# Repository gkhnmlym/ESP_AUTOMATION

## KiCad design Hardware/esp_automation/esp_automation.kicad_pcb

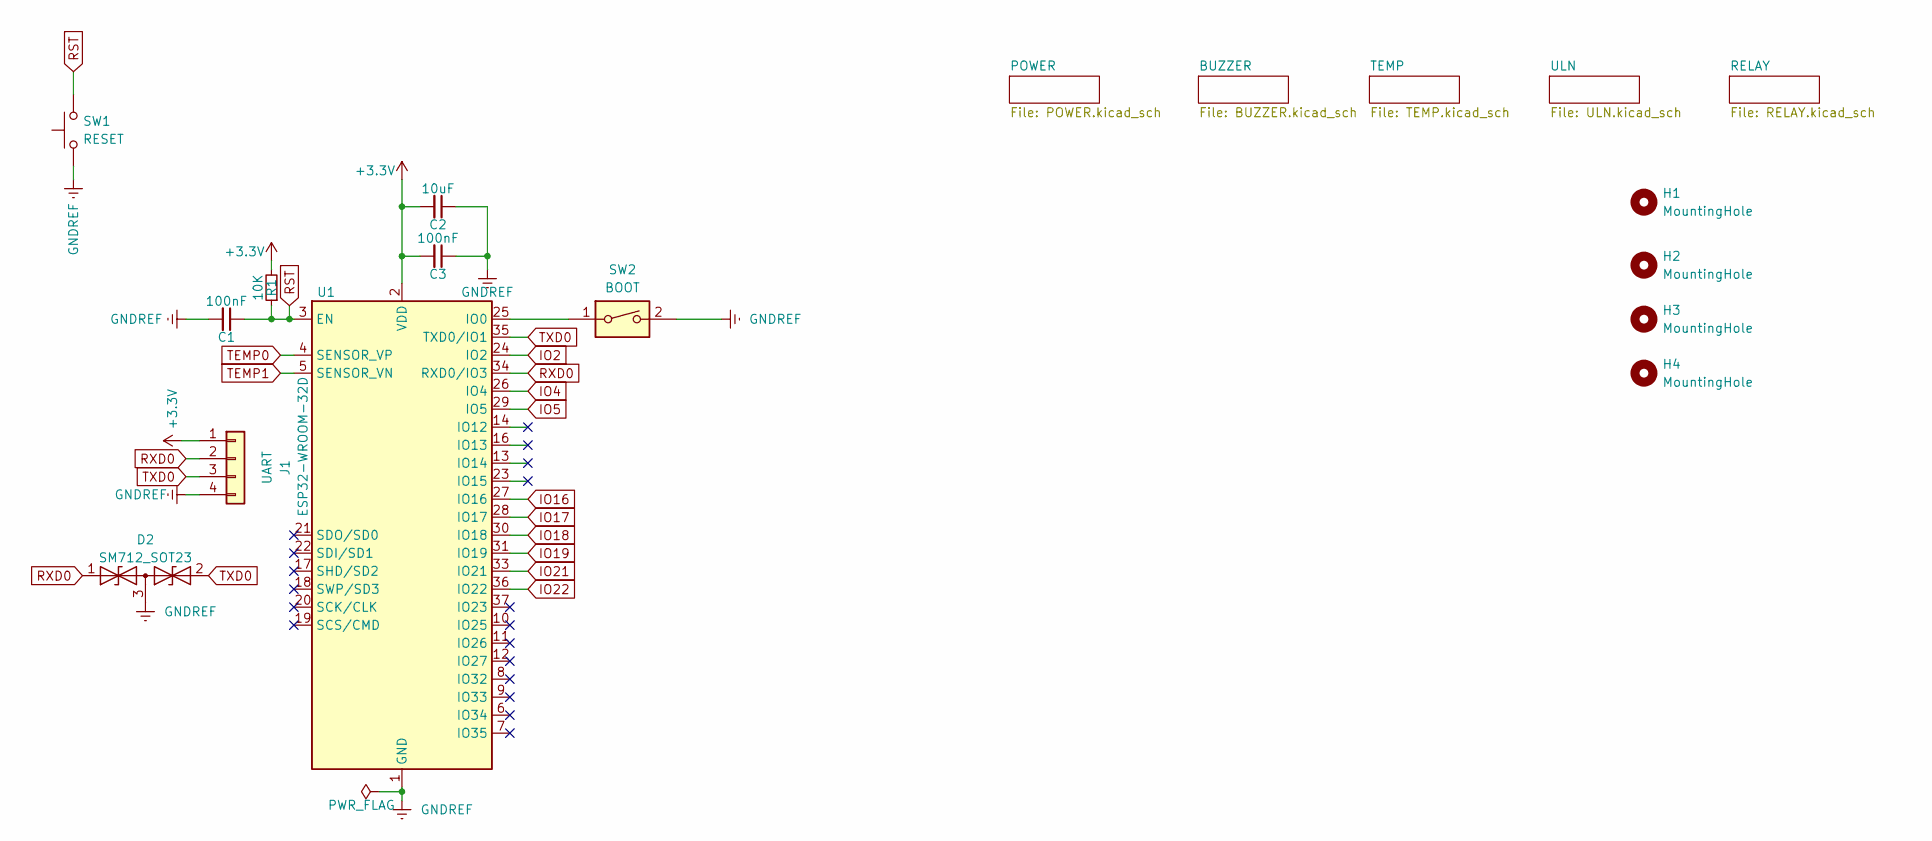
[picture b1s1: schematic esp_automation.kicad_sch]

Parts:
C1, C3: 100nF; C_0805_2012Metric
C2: 10uF; C_0805_2012Metric
D2: SM712_SOT23; SOT-23
H1, H2, H3, H4: MountingHole; MountingHole_3.2mm_M3_Pad_Via
J1: UART; PinHeader_1x04_P2.54mm_Vertical
R1: 10K; R_0805_2012Metric
SW1: RESET; SW_SPST_CK_RS282G05A3
SW2: BOOT; SW_DIP_SPSTx01_Slide_6.7x4.1mm_W6.73mm_P2.54mm_LowProfile_J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
U1: ESP32-WROOM-32D; ESP32-WROOM-32

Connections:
+3V3: C2.2, C3.2, J1.1, R1.2, U1.2 (VDD); also elsewhere on the board
IO2: U1.24 (IO2)
IO4: U1.26 (IO4); also elsewhere on the board
IO5: U1.29 (IO5); also elsewhere on the board
IO16: U1.27 (IO16); also elsewhere on the board
IO17: U1.28 (IO17); also elsewhere on the board
IO18: U1.30 (IO18); also elsewhere on the board
IO19: U1.31 (IO19); also elsewhere on the board
IO21: U1.33 (IO21); also elsewhere on the board
IO22: U1.36 (IO22); also elsewhere on the board
unnamed: SW2.1, U1.25 (IO0)
RST: C1.1, R1.1, SW1.2, U1.3 (EN)
RXD0: D2.1 (A1), J1.2, U1.34 (RXD0/IO3)
TEMP0: U1.4 (SENSOR_VP); also elsewhere on the board
TEMP1: U1.5 (SENSOR_VN); also elsewhere on the board
TXD0: D2.2 (A2), J1.3, U1.35 (TXD0/IO1)

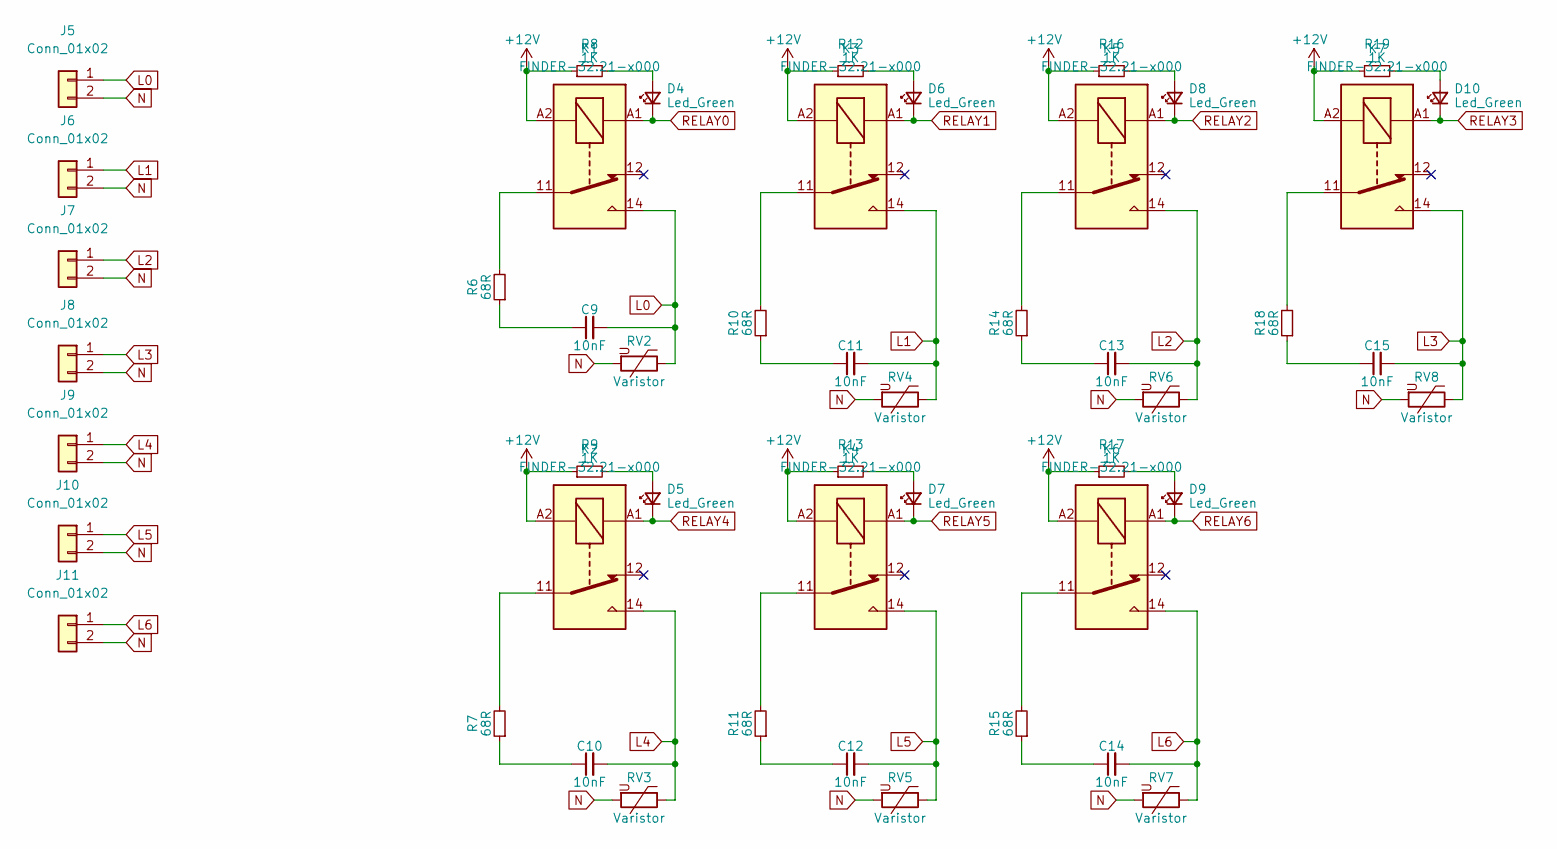
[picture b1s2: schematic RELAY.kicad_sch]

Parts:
C9, C10, C11, C12, C13, C14, C15: 10nF; C_Rect_L13.0mm_W4.0mm_P10.00mm_FKS3_FKP3_MKS4
D4, D5, D6, D7, D8, D9, D10: Led_Green; LED_0805_2012Metric
J5, J6, J7, J8, J9, J10, J11: Conn_01x02; TerminalBlock_Phoenix_MKDS-1,5-2-5.08_1x02_P5.08mm_Horizont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
K1, K2, K3, K4, K5, K6, K7: FINDER-32.21-x000; Relay_SPDT_Finder_32.21-x000
R6, R7, R10, R11, R14, R15, R18: 68R; R_2512_6332Metric
R8, R9, R12, R13, R16, R17, R19: 1K; R_0805_2012Metric
RV2, RV3, RV4, RV5, RV6, RV7, RV8: Varistor; RV_Disc_D9mm_W4mm_P5mm

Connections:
+12V: K1.A2, K2.A2, K3.A2, K4.A2, K5.A2, K6.A2, K7.A2, R8.1, R9.1, R12.1, R13.1, R16.1, R17.1, R19.1; also elsewhere on the board
L0: C9.2, J5.1, K1.14, RV2.1
L1: C11.2, J6.1, K3.14, RV4.1
L2: C13.2, J7.1, K5.14, RV6.1
L3: C15.2, J8.1, K7.14, RV8.1
L4: C10.2, J9.1, K2.14, RV3.1
L5: C12.2, J10.1, K4.14, RV5.1
L6: C14.2, J11.1, K6.14, RV7.1
N: J5.2, J6.2, J7.2, J8.2, J9.2, J10.2, J11.2, RV2.2, RV3.2, RV4.2, RV5.2, RV6.2, RV7.2, RV8.2; also elsewhere on the board
unnamed: C9.1, R6.1
unnamed: C10.1, R7.1
unnamed: C11.1, R10.1
unnamed: C12.1, R11.1
unnamed: C13.1, R14.1
unnamed: C14.1, R15.1
unnamed: C15.1, R18.1
unnamed: D4.2 (A), R8.2
unnamed: D5.2 (A), R9.2
unnamed: D6.2 (A), R12.2
unnamed: D7.2 (A), R13.2
unnamed: D9.2 (A), R17.2
unnamed: D10.2 (A), R19.2
unnamed: K1.11, R6.2
unnamed: K2.11, R7.2
unnamed: K3.11, R10.2
unnamed: K4.11, R11.2
unnamed: K5.11, R14.2
unnamed: K6.11, R15.2
unnamed: K7.11, R18.2
RELAY0: D4.1 (K), K1.A1; also elsewhere on the board
RELAY1: D6.1 (K), K3.A1; also elsewhere on the board
RELAY3: D10.1 (K), K7.A1; also elsewhere on the board
RELAY4: D5.1 (K), K2.A1; also elsewhere on the board
RELAY5: D7.1 (K), K4.A1; also elsewhere on the board
RELAY6: D9.1 (K), K6.A1; also elsewhere on the board

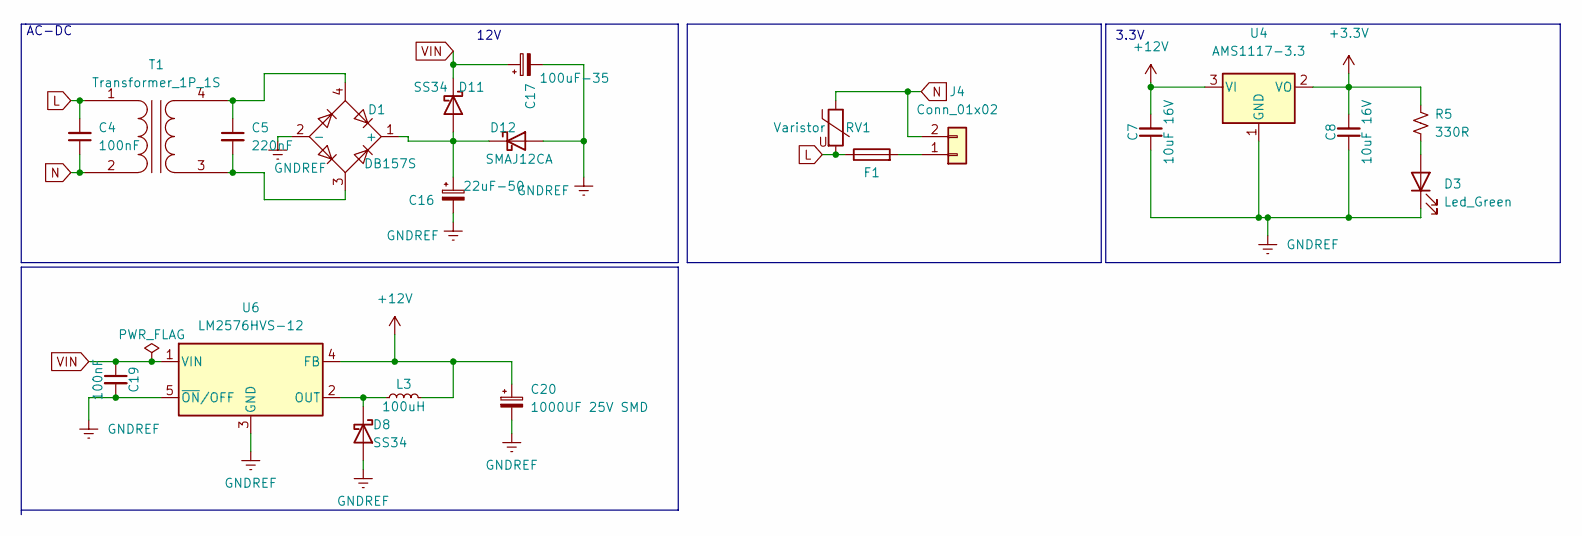
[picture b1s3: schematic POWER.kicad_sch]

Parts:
C4: 100nF; C_Rect_L18.0mm_W6.0mm_P15.00mm_FKS3_FKP3
C5: 220nF; C_Rect_L13.0mm_W8.0mm_P10.00mm_FKS3_FKP3_MKS4
C7, C8: 10uF 16V; C_0805_2012Metric
C16: 22uF-50; CP_Elec_6.3x7.7
C17: 100uF-35; CP_Elec_6.3x7.7
C19: 100nF; C_0805_2012Metric
C20: 1000UF 25V SMD; CP_Elec_10x12.6
D1: DB157S
D3: Led_Green; LED_0805_2012Metric
D8: SS34; D_SMC
D11: SS34; D_SMB
D12: SMAJ12CA; D_SMB
F1: MFS1630A - FUSE 6.3A 250V; Fuse_Littelfuse_395Series
J4: Conn_01x02; TerminalBlock_Phoenix_MKDS-1,5-2-5.08_1x02_P5.08mm_Horizont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
L3: 100uH; L_12x12mm_H4.5mm
R5: 330R; R_0805_2012Metric
RV1: Varistor; RV_Disc_D12mm_W5mm_P7.5mm
T1: Transformer_1P_1S; ASLAN 151112
U4: AMS1117-3.3; SOT-223-3_TabPin2
U6: LM2576HVS-12; TO-263-5_TabPin3

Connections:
+3V3: C8.2, R5.2, U4.2 (VO); also elsewhere on the board
+12V: C7.2, U4.3 (VI); also elsewhere on the board
L: C4.2, F1.1, RV1.2, T1.1 (AA)
N: C4.1, J4.2, RV1.1, T1.2 (AB); also elsewhere on the board
unnamed: C16.1, D1.1 (+), D11.2 (A), D12.1 (K)
unnamed: D3.2 (A), R5.1
unnamed: F1.2, J4.1
unnamed: C5.2, D1.3, T1.3 (SA)
unnamed: C5.1, D1.4, T1.4 (SB)
VIN: C17.1, C19.1, D11.1 (K); also elsewhere on the board

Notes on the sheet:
AC-DC
3.3V
12V

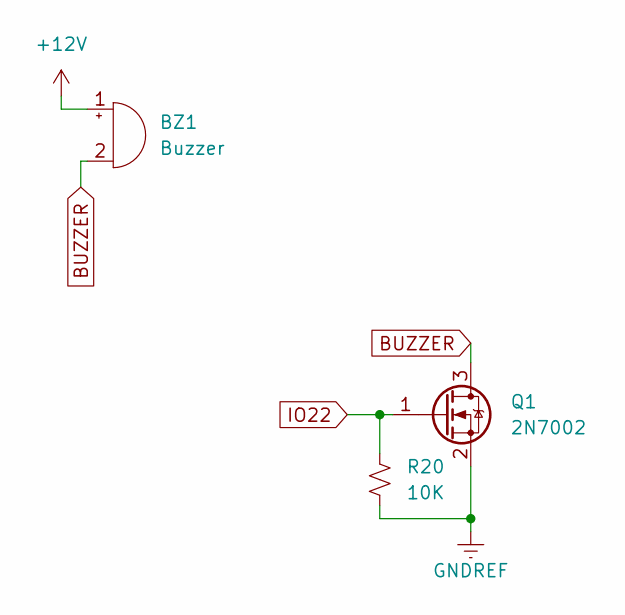
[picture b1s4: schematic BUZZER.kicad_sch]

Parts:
BZ1: Buzzer; Buzzer_CUI_CPT-9019S-SMT
Q1: 2N7002; SOT-23
R20: 10K; R_0805_2012Metric

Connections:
+12V: BZ1.1 (-); also elsewhere on the board
BUZZER: BZ1.2 (+), Q1.3 (D)
IO22: Q1.1 (G), R20.1; also elsewhere on the board

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
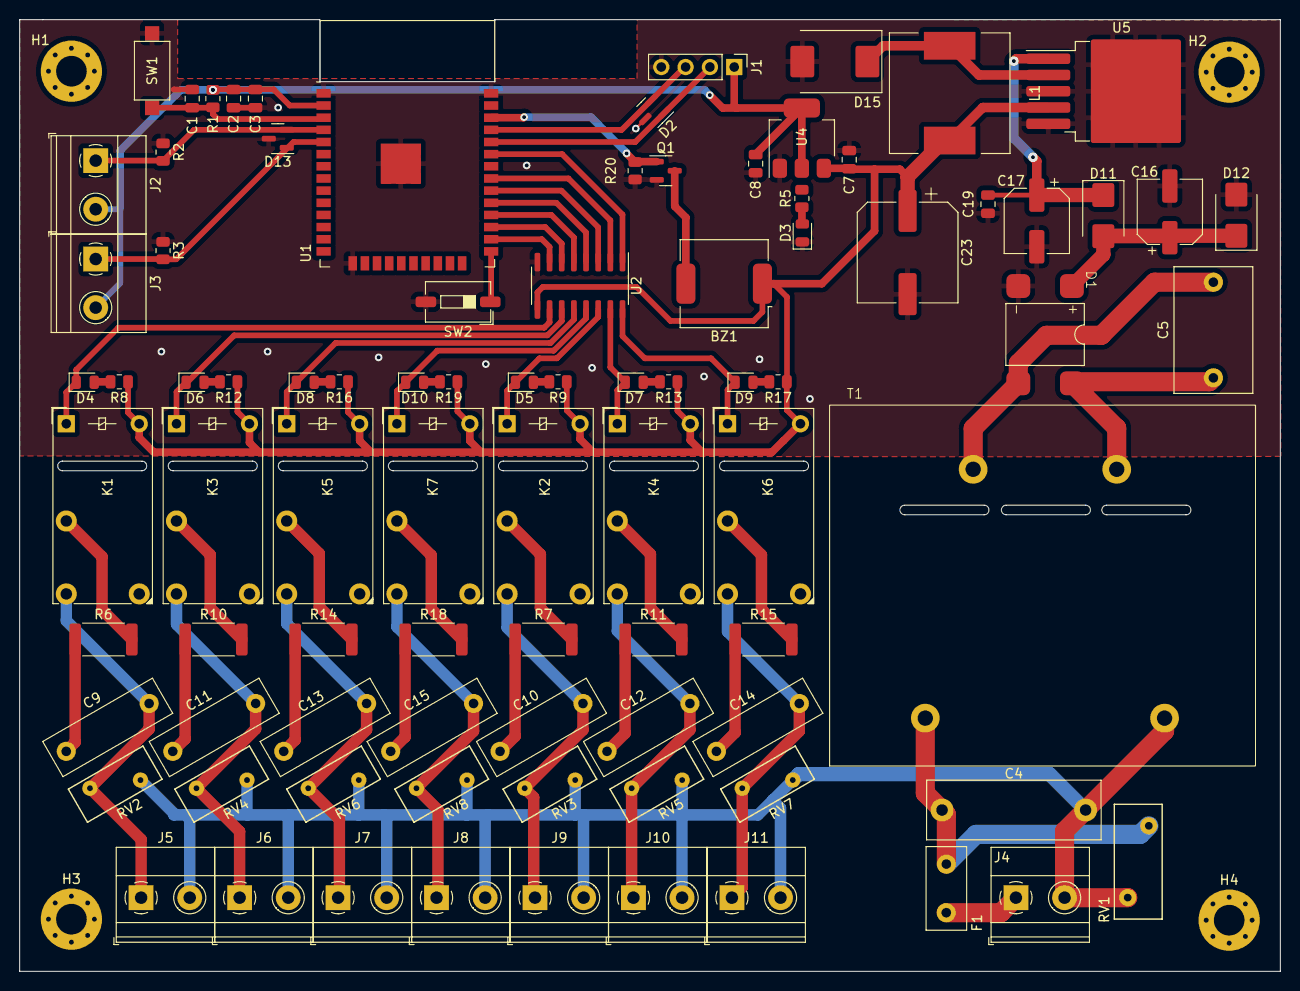
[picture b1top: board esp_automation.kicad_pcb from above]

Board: 2 copper layers, 131.7 x 99.4 mm, 92 parts (0 on the bottom side), 62 nets.

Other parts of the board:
C23: 1000UF 25V SMD; CP_Elec_10x12.6
D13: SM712_SOT23; SOT-23
D15: SS34; D_SMC
J2: TEMP0; TerminalBlock_Phoenix_MKDS-1,5-2-5.08_1x02_P5.08mm_Horizont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
J3: TEMP1; TerminalBlock_Phoenix_MKDS-1,5-2-5.08_1x02_P5.08mm_Horizont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
L1: 100uH; L_12x12mm_H4.5mm
R2, R3: 10K; R_0805_2012Metric
U2: ULN2003A; SOIC-16_3.9x9.9mm_P1.27mm
U5: LM2576HVS-12; TO-263-5_TabPin3

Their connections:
+3V3: J2.2, J3.2; also elsewhere on the board
+12V: C23.1, L1.2, U2.9 (COM), U5.4 (FB); also elsewhere on the board
IO4: U2.7 (I7); also elsewhere on the board
IO5: U2.4 (I4); also elsewhere on the board
IO16: U2.6 (I6); also elsewhere on the board
IO17: U2.5 (I5); also elsewhere on the board
IO18: U2.3 (I3); also elsewhere on the board
IO19: U2.2 (I2); also elsewhere on the board
IO21: U2.1 (I1); also elsewhere on the board
RELAY0: U2.10 (O7); also elsewhere on the board
RELAY1: U2.11 (O6); also elsewhere on the board
RELAY3: U2.13 (O4); also elsewhere on the board
RELAY4: U2.14 (O3); also elsewhere on the board
RELAY5: U2.15 (O2); also elsewhere on the board
RELAY6: U2.16 (O1); also elsewhere on the board
TEMP0: D13.2 (A2), J2.1, R2.1; also elsewhere on the board
TEMP1: D13.1 (A1), J3.1, R3.1; also elsewhere on the board
VIN: U5.1 (VIN); also elsewhere on the board

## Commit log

2023-04-27 Upload
2023-07-06 add software
